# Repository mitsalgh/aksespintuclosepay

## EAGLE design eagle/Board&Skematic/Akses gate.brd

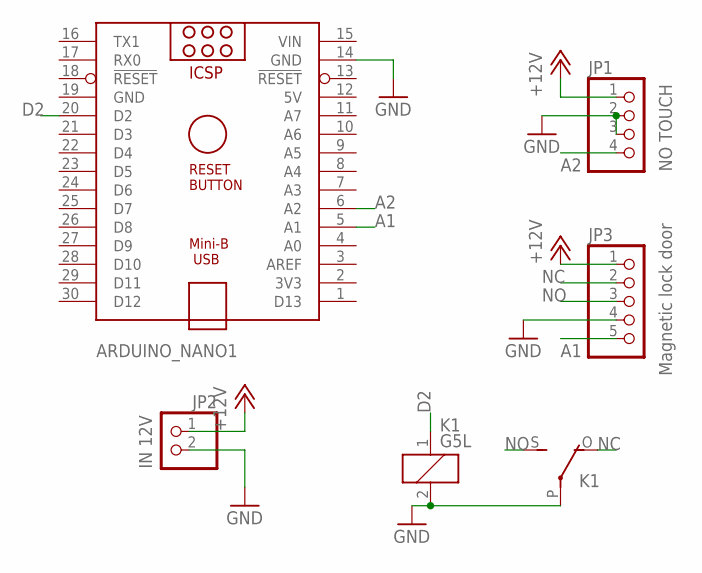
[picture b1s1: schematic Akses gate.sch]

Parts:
ARDUINO_NANO1: ARDUINO_NANO
JP1: PINHD-1X4; 1X04
JP2: PINHD-1X2; 1X02
JP3: PINHD-1X5; 1X05
K1: G5L; G5LE

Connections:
5V: ARDUINO_NANO1.12 (5V)
+12V: JP1.1, JP2.1, JP3.1
A1: ARDUINO_NANO1.5 (A1), JP3.5
A2: ARDUINO_NANO1.6 (A2), JP1.4
D2: ARDUINO_NANO1.20 (D2), K1.1
GND: ARDUINO_NANO1.14 (GND), ARDUINO_NANO1.19 (GND), JP1.2, JP1.3, JP2.2, JP3.4, K1.2, K1.P
NC: JP3.2, K1.O
NO: JP3.3, K1.S
VIN: ARDUINO_NANO1.15 (VIN)

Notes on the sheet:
IN 12V
NO TOUCH
Magnetic lock door

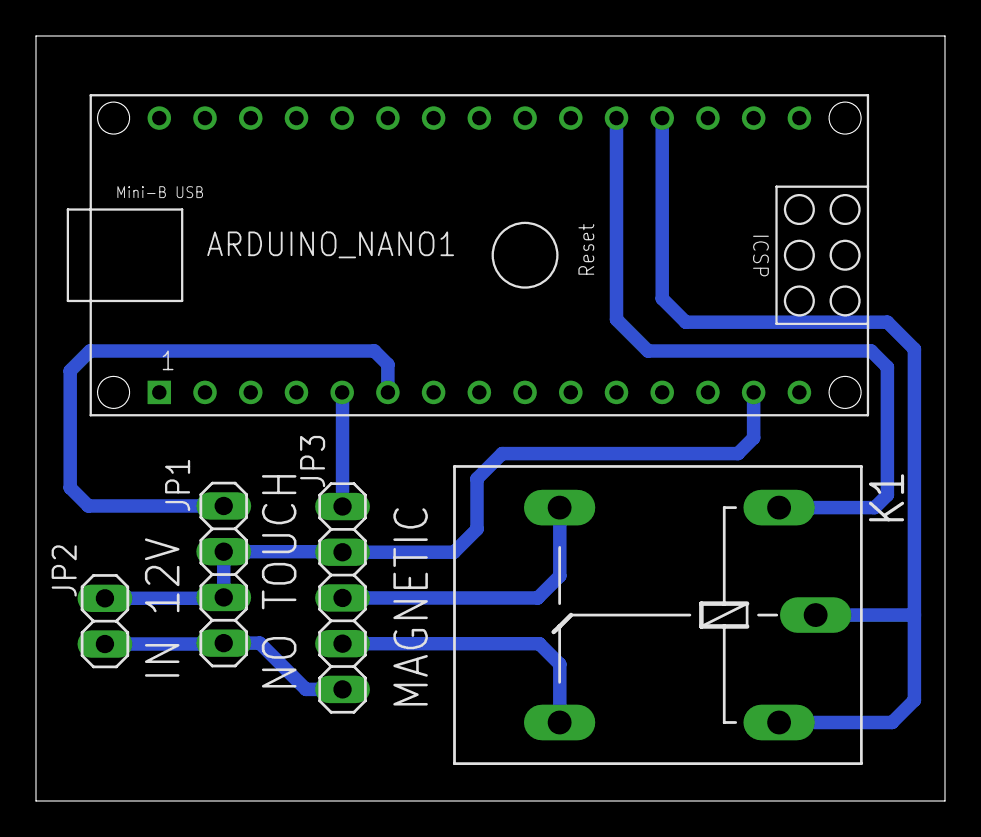
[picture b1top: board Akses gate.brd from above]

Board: 2 copper layers, 50.5 x 42.5 mm, 5 parts (0 on the bottom side), 7 nets.
